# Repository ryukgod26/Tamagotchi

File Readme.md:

# Tamagotchi
This is a Tamagotchi Created by me for fun and experiment. This uses Arduino Nano as the Processor. I have also created a Basic 3D Model for this Project.

## Required Electronics
 - Ardunino Nano x 1
 - 1000mah Battery x 1
 - Charging module x 1
 - 128X64 OLED Display x 1
 - Push Buttons x 3
 - Slide Switch x 1

## Why
I created this Project to Create a Compact device by using many non smd components. I just wanted to create something that I can Play wit in free time.

## Zine

## 3D Model Instructions

There are 4 Panels for the 3D Model. Firstly, We attach the Panel 1 and Panel 2 Together with Glue. Then we attach the Panel 3 and Panel 4 together with Glue. Then We attach the components inside them according to the cutouts Like Panel1 is for Oled Display, Panel 2 is for Battery , Panel 3 is for charging module and Panel 4 is for Arduino Nano. Wire them together according to the schmatics and upload the code to the Arduino Nano.

### Panel 1

### Panel 2

### Panel 3

### Panel 4

### Panel1 and Panel2 Glued Together

### Panel3 and Panel4 Glued Together

### Shell

# BOM (Bill of Materials)

|Name| Purpose | Quantity| Total Cost (USD) | Link | Distributor|
|----|---------|---------|------------------|------|------------|
| Arduino Nano | Processor | 1 | $2.00 | [robu](https://robu.in/product/arduino-nano-board-r3-with-ch340-chip-wo-usb-cable-solderedarduino-nano-r3-wo-usb-cable-soldered/) | Robu |
| OLED Display | Display | 1 | $2.2 | [robu](https://robu.in/product/0-96-inch-ssd1306-white-oled-display-module/) | Robu |
| Slide Switch | Power Switch | 1 | $0.3 | [robu](https://robu.in/product/ss12d10g5-wj-shou-han-bend-insert-2a-single-pole-double-throw-spdt-125v-3000-times-black-plugin-slide-switches-rohs/) | Robu |
| Charging Module | Charging Module | 1 | $1.9 | [robu](https://robu.in/product/tp4056-3-7v-lithium-battery-charging-module-1a-usb-type-c-port-ph2-0-terminal/) | Robu |
| Push Buttons | Buttons | 10 (only 3 are needed) | $0.2 | [robu](https://robu.in/product/6x6x5-tactile-push-button-switch/) | Robu |
| Lithium Battery | Battery | 1 | $4 | [robu](https://robu.in/product/wly803040-1000mah-3-7v-single-cell-rechargeable-lipo-battery/) | Robu |

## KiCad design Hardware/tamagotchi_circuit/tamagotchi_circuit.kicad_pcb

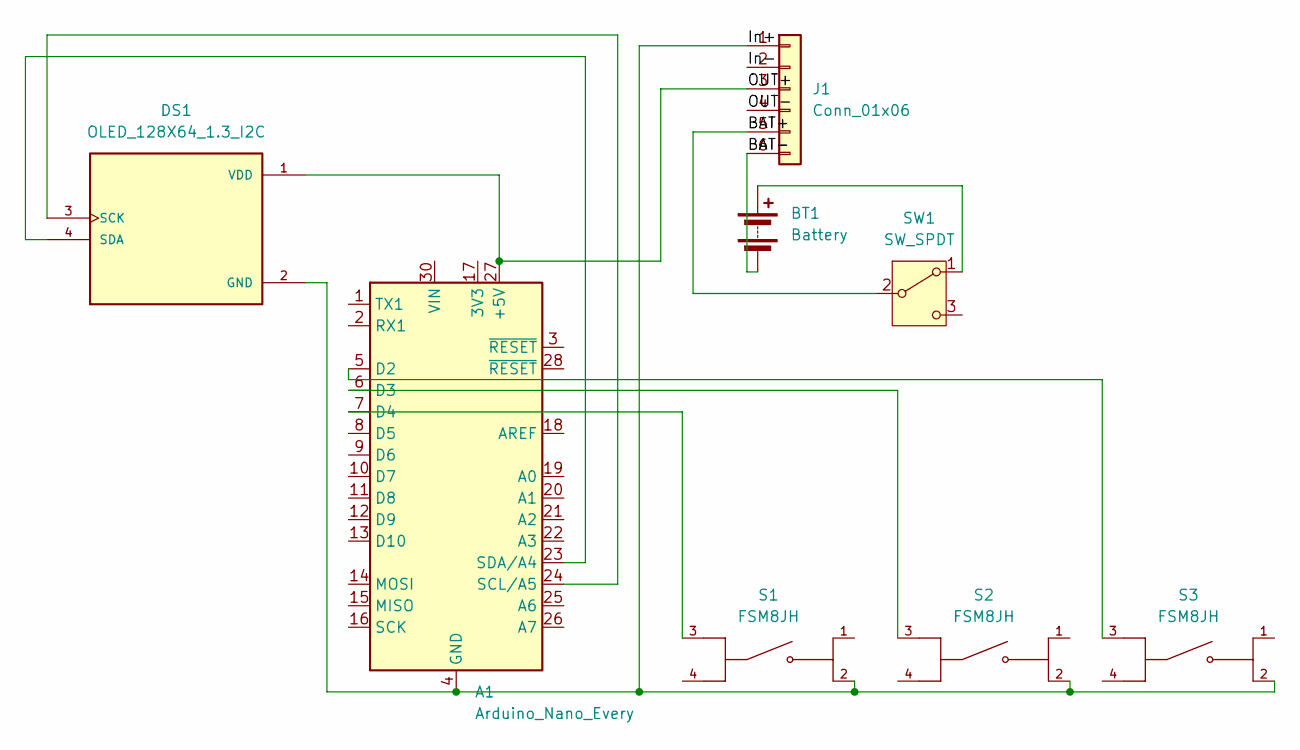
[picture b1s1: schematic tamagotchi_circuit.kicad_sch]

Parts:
A1: Arduino_Nano_Every; Arduino_Nano
BT1: Battery; Battery_Panasonic_CR1025-VSK_Vertical_CircularHoles
DS1: OLED_128X64_1.3_I2C; LCD_OLED_128X64_1.3_I2C; PARTREV NA
J1: Conn_01x06; TP4056-18650
S1, S2, S3: FSM8JH; SW_FSM8JH; PARTREV 8-1773450-9
SW1: SW_SPDT; SW_EG1218

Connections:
/BAT+: J1.5, SW1.2 (B)
/BAT-: BT1.2 (-), J1.6
/In+: A1.4 (GND), A1.29 (GND), DS1.2 (GND), J1.1, S1.2, S2.2, S3.2
/In-: J1.2
/OUT+: A1.27 (+5V), DS1.1 (VDD), J1.3
/OUT-: J1.4
unnamed: A1.5 (D2), S3.3
unnamed: A1.6 (D3), S2.3
unnamed: A1.7 (D4), S1.3
unnamed: A1.24 (SCL/A5), DS1.3 (SCK)
unnamed: A1.23 (SDA/A4), DS1.4 (SDA)
unnamed: BT1.1 (+), SW1.1 (A)

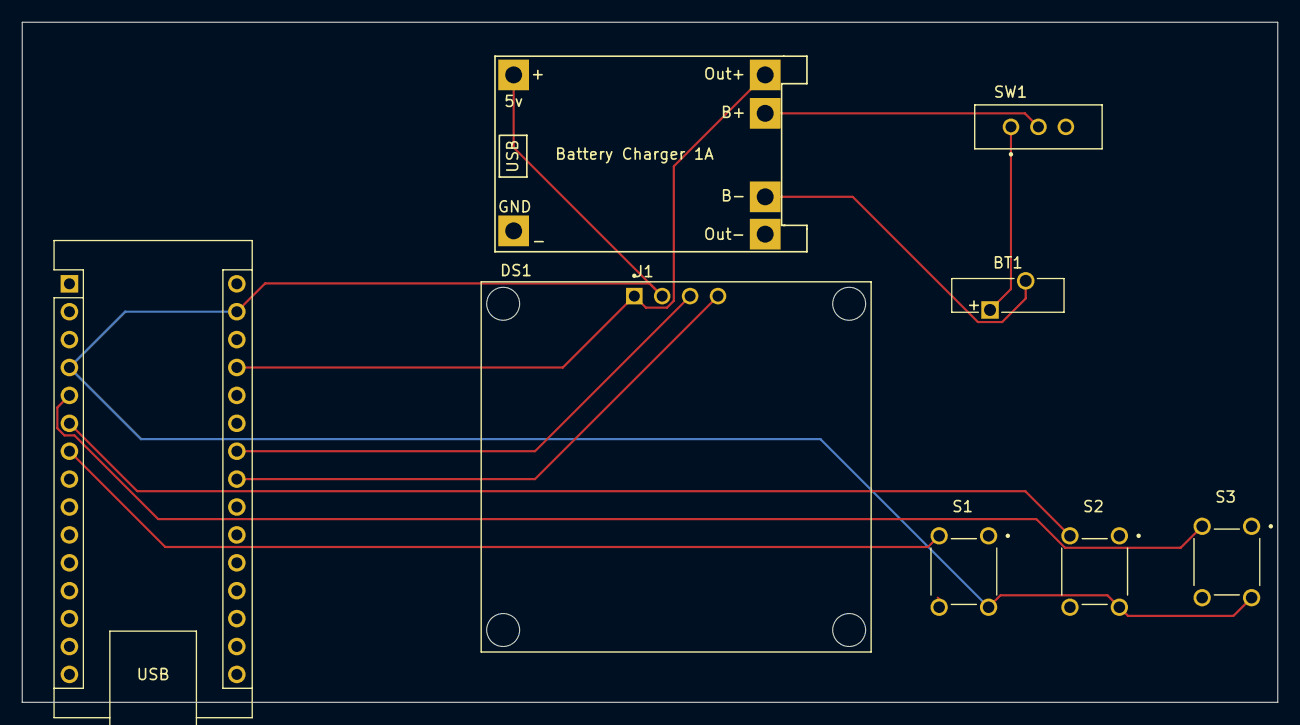
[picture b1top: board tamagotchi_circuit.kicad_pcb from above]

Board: 2 copper layers, 114.3 x 61.9 mm, 8 parts (0 on the bottom side), 10 nets.

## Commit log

2026-05-23 Added First Panel for the 3D models of the tamagotchi
2026-05-24 Added Panel2 and changed the Panel1 Base Shape from circle to ellipse
2026-05-24 Added Panel3 in the 3D Models
2026-05-25 Added Panel4 of the tamagotchi
2026-05-26 Added Schematics and PCb for the pcb
2026-05-27 Added 3D models ofthe electronic components and merged them with the panels
2026-06-02 Added Code Files for the Project
2026-06-02 Added Readme Journala and 3D Model Images
2026-06-02 Fixed Slashes in readme
2026-06-02 Added Bill of materials
2026-06-02 Fixed a typo
2026-06-02 Fixed missing brackets in readme
2026-06-18 Update circuit schematic footprints, add new images, and enhance documentation
    - Updated footprints for components in the tamagotchi circuit schematic.
    - Added new images including Front.PNG, QRCODE.png, QR_TRANSPARENT.png, arduino_transparent.png, screen_Front_transparent.png, and shell.png.
    - Updated the README.md to include a section for the shell image.
    - Added new zine files: Tamagotchi Zine.pdf and Tamagotchi Zine.png.
2026-06-21 Add Gerber files and drill files for Tamagotchi circuit; update README and zine assets
    - Created non-plated and plated drill files for the Tamagotchi circuit.
    - Added a job file for Gerber output specifications.
    - Included a ZIP file for PCB assets.
    - Updated README to include a new zine image.
    - Removed outdated zine PDF and PNG files.
    - Added new zine images in JPG, PDF, and PNG formats.
2026-06-21 Add project description to README and update zine images
